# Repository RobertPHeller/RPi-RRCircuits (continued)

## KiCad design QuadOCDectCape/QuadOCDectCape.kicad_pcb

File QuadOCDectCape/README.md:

# QuadOCDectCape

Quad Occupancy detector Cape (for a Beagle Bone).

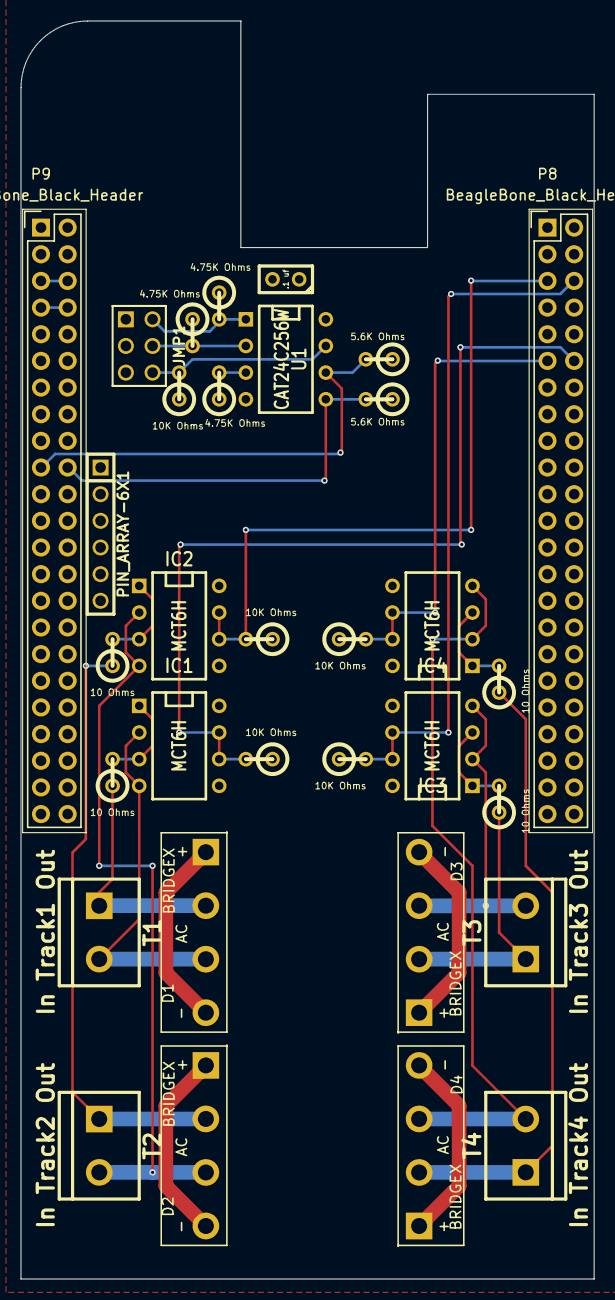
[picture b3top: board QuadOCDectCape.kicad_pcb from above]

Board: 2 copper layers, 54.6 x 119.9 mm, 32 parts (0 on the bottom side), 30 nets.

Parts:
C1: .1 uf; C1
D1, D2, D3, D4: BRIDGEX; KBL
IC1, IC2, IC3, IC4: MCT6H; DIP-8__300
JMP1: WP 1 0; pin_array_3x2
P8, P9: BeagleBone_Black_Header; Socket_BeagleBone_Black
PIN_ARRAY-6X1: Val**; PIN_ARRAY-6X1
R1, R3, R5, R7: 10 Ohms; R1
R2, R4, R6, R8, R14: 10K Ohms; R1
R9, R10: 5.6K Ohms; R1
R11, R12, R13: 4.75K Ohms; R1
T1: In Track1 Out; bornier2
T2: In Track2 Out; bornier2
T3: In Track3 Out; bornier2
T4: In Track4 Out; bornier2
U1: CAT24C256W; DIP-8__300

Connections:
+3.3V: C1.1, P9.3, P9.4, R2.1, R4.1, R6.1, R8.1, R9.1, R10.1, R11.1, R12.1, R13.1, R14.1, U1.8
+5V: P9.5, P9.6
/Cape EEProm/SCL: P9.19, R10.2, U1.6
/Cape EEProm/SDA: P9.20, R9.2, U1.5
/Occupancy Detector 1/OD1: IC1.6, IC1.7, P8.12, R2.2
/Occupancy Detector 2/OD2: IC2.6, IC2.7, P8.5, R4.2
/Occupancy Detector 3/OD3: IC3.6, IC3.7, P8.6, R6.2
/Occupancy Detector 4/OD4: IC4.6, IC4.7, P8.11, R8.2
GND: C1.2, IC1.5, IC1.8, IC2.5, IC2.8, IC3.5, IC3.8, IC4.5, IC4.8, JMP1.1, JMP1.3, JMP1.5, P8.1, P8.2, P9.1, P9.2, P9.43, P9.44, P9.45, P9.46, U1.4
unnamed: IC4.1, IC4.3, R7.2
unnamed: D4.3, IC4.2, IC4.4, T4.2
unnamed: D4.2, R7.1, T4.1
unnamed: D4.1, D4.4
unnamed: JMP1.6, R14.2, U1.7
unnamed: JMP1.2, R11.2, U1.1
unnamed: JMP1.4, R12.2, U1.2
unnamed: R13.2, U1.3
unnamed: IC1.1, IC1.3, R1.2
unnamed: D1.3, IC1.2, IC1.4, T1.2
unnamed: D1.2, R1.1, T1.1
unnamed: D1.1, D1.4
unnamed: D2.2, R3.1, T2.1
unnamed: D2.1, D2.4
unnamed: D2.3, IC2.2, IC2.4, T2.2
unnamed: IC2.1, IC2.3, R3.2
unnamed: D3.3, IC3.2, IC3.4, T3.2
unnamed: IC3.1, IC3.3, R5.2
unnamed: D3.2, R5.1, T3.1
unnamed: D3.1, D3.4
SYS_5V: P9.7, P9.8

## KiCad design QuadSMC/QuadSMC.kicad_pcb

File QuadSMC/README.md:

# QuadSMC

This is a generic quad verison of SMCSenseHAT.

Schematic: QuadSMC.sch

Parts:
C1, C2: .1 uf; Mouser Part Number 21RZ310-RC
C3, C4: 1 uf 35V; Mouser Part Number 74-199D105X9035A1VE3
D1, D6: 1N5229B; Mouser Part Number 512-1N5229B
D2, D3, D4, D5: 1N4002; Mouser Part Number 833-1N4002-TP
IC1, IC2: MCT6H; DIP8; Mouser Part Number 782-MCT6H
Q1, Q2: MPQ3725A; DIP-14__300; Mouser Part Number 610-MPQ3725A
R1: 10K Ohms; Mouser Part Number 652-4609X-1LF-10K
R2, R3, R4, R5: 270 Ohms; Mouser Part Number 71-CCF07270RGKE36
R6, R7, R8, R9: 100 Ohms; Mouser Part Number 71-CCF07100RJKE36
R10, R11, R12, R13, R14, R15, R16, R17, R18, R19, R20, R21, R22, R23: 1K Ohms; Mouser Part Number 71-CCF071K00JKE36
R24, R25, R26, R27, R28, R29, R30, R31: 470 Ohms; Mouser Part Number 279-CFR50J470R
T0: GPIO; Mouser Part Number 651-1725737
T1: Motor 1; Mouser Part Number 571-282834-5
T2: Motor 2; Mouser Part Number 571-282834-5
T3: Motor 3; Mouser Part Number 571-282834-5
T4: Motor 4; Mouser Part Number 571-282834-5
T5: Motor Power; SIL-2; Mouser Part Number 571-282834-2
U1, U2: 74AHCT00; Mouser Part Number 595-SN74AHC00N
U3, U4: LM324N; Mouser Part Number 512-LM324N

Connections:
+3.3V: C1.1, C2.1, R1.1, T0.1, U1.14 (VCC), U2.14 (VCC)
+12V: C3.1, C4.1, R10.1, R11.1, R12.1, R13.1, R14.1, R15.1, R24.1, R25.1, R26.1, R27.1, R28.1, R29.1, R30.1, R31.1, T5.1, U3.4 (V+), U4.4 (V+)
/GPIO0: R5.2, T0.9
/GPIO1: T0.8, U2.8, U2.12
/GPIO2: R3.2, T0.7
/GPIO3: T0.6, U2.3, U2.4
/GPIO4: R2.2, T0.5
/GPIO5: T0.4, U1.8, U1.12
/GPIO6: R4.2, T0.3
/GPIO7: T0.2, U1.3, U1.4
/P1-1: R1.2, T1.5, U1.1
/P1-2: R1.3, T1.3, U1.5
/P2-1: R1.4, T2.5, U1.9
/P2-2: R1.5, T2.3, U1.13
/P3-1: R1.6, T3.5, U2.1
/P3-2: R1.7, T3.3, U2.5
/P4-1: R1.8, T4.5, U2.9
/P4-2: R1.9, T4.3, U2.13
GND: C1.2, C2.2, C3.2, C4.2, D1.1 (A), D6.1 (A), IC1.2, IC1.3, IC1.5, IC1.8, IC2.2, IC2.3, IC2.5, IC2.8, Q1.3 (E), Q1.5 (E), Q1.10 (E), Q1.12 (E), Q2.3 (E), Q2.5 (E), Q2.10 (E), Q2.12 (E), T0.10, T1.4, T2.4, T3.4, T4.4, T5.2 (PM), U1.7 (GND), U2.7 (GND), U3.11 (V-), U4.11 (V-)
M1A: Q1.1 (C), R24.2, T1.2
M1B: Q1.7 (C), R25.2, T1.1
M2A: Q1.8 (C), R26.2, T2.2
M2B: Q1.14 (C), R27.2, T2.1
M3A: Q2.1 (C), R28.2, T3.2
M3B: Q2.7 (C), R29.2, T3.1
M4A: Q2.8 (C), R30.2, T4.2
M4B: Q2.14 (C), R31.2, T4.1
unnamed: Q2.6 (B), R22.1
unnamed: Q2.9 (B), R23.1
unnamed: Q2.13 (B), R16.1
unnamed: R16.2, U4.7
unnamed: D4.1 (A), R6.1, R10.2, U3.2 (-), U3.12 (+)
unnamed: R18.2, U3.14
unnamed: Q1.6 (B), R18.1
unnamed: D5.1 (A), R7.1, R11.2, U3.5 (+), U3.9 (-)
unnamed: IC1.6, R7.2
unnamed: IC1.7, R6.2
unnamed: IC2.7, R8.2
unnamed: D2.1 (A), R8.1, R12.2, U4.2 (-), U4.12 (+)
unnamed: IC2.6, R9.2
unnamed: D3.1 (A), R9.1, R13.2, U4.5 (+), U4.9 (-)
unnamed: D1.2 (K), D4.2 (K), D5.2 (K), R15.2, U3.3 (+), U3.6 (-), U3.10 (+), U3.13 (-)
unnamed: D2.2 (K), D3.2 (K), D6.2 (K), R14.2, U4.3 (+), U4.6 (-), U4.10 (+), U4.13 (-)
unnamed: R20.2, U3.7
unnamed: R21.2, U4.1
unnamed: R22.2, U4.14
unnamed: R23.2, U4.8
unnamed: Q1.2 (B), R17.1
unnamed: R17.2, U3.1
unnamed: R19.2, U3.8
unnamed: Q1.9 (B), R19.1
unnamed: Q1.13 (B), R20.1
unnamed: Q2.2 (B), R21.1
unnamed: IC2.4, R5.1
unnamed: IC1.1, R4.1
unnamed: IC1.4, R2.1
unnamed: IC2.1, R3.1
unnamed: U2.2, U2.6
unnamed: U2.10, U2.11
unnamed: U1.2, U1.6
unnamed: U1.10, U1.11

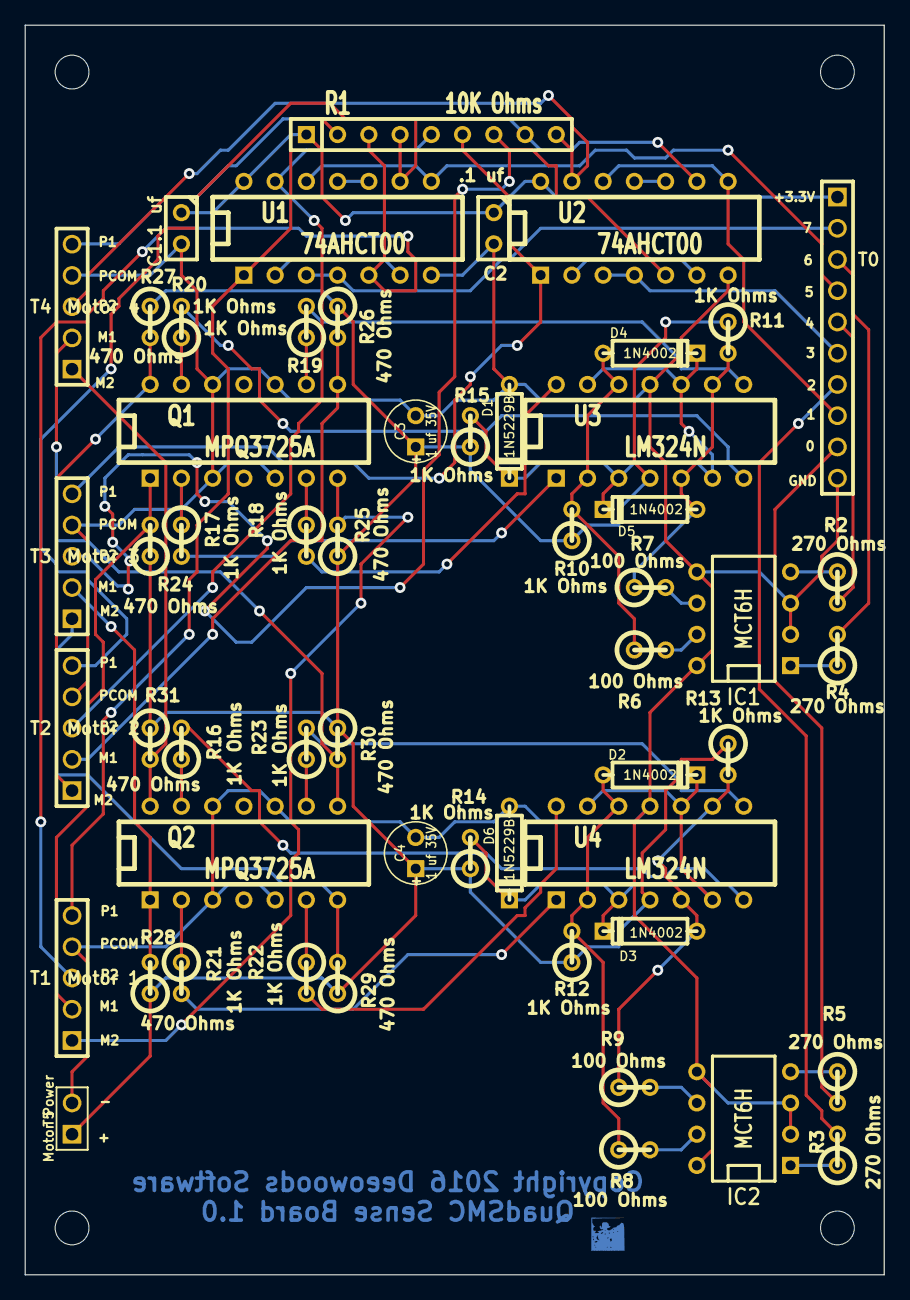
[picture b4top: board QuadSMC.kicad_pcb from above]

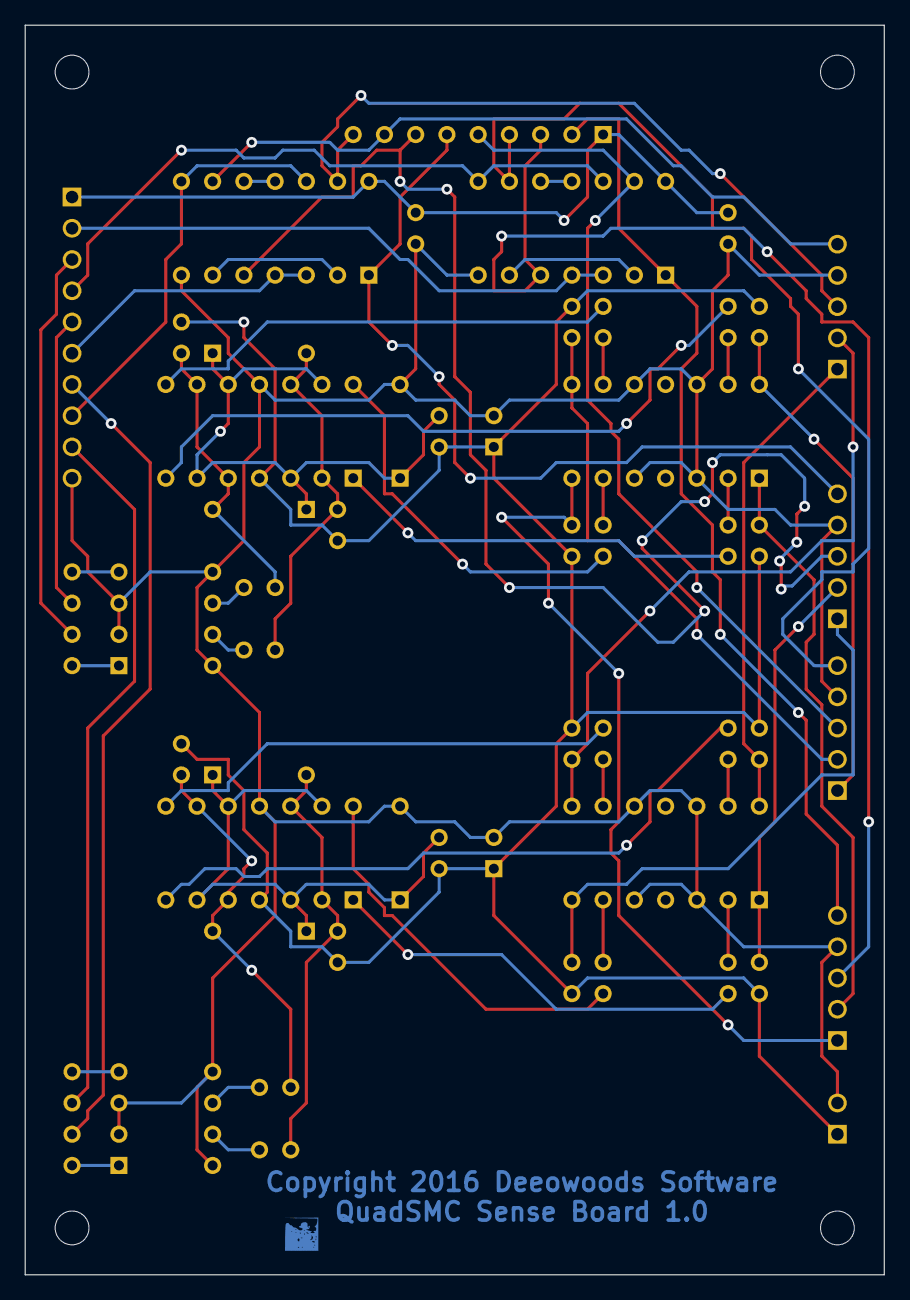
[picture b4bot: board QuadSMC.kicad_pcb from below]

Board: 2 copper layers, 69.8 x 101.6 mm, 59 parts (4 on the bottom side), 61 nets.

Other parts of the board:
H2, H2#2, H2#3, H2#4: RPi_Hat_Mounting_Hole

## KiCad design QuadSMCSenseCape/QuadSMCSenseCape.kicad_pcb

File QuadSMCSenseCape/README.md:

# QuadSMCSenseCape

Quad Stall Motor w/ Sense Cape for a Beagle Bone.

* [Order this board from The Country Robot](https://www.thecountryrobot.com/product/quad-stall-motor-control-and-sense-cape-for-beagle-bare-circuit-board-w-doc/)
* [Order this board from PCBWay](https://www.pcbway.com/project/shareproject/Quad_Stall_motor_with_point_sense_cape.html)

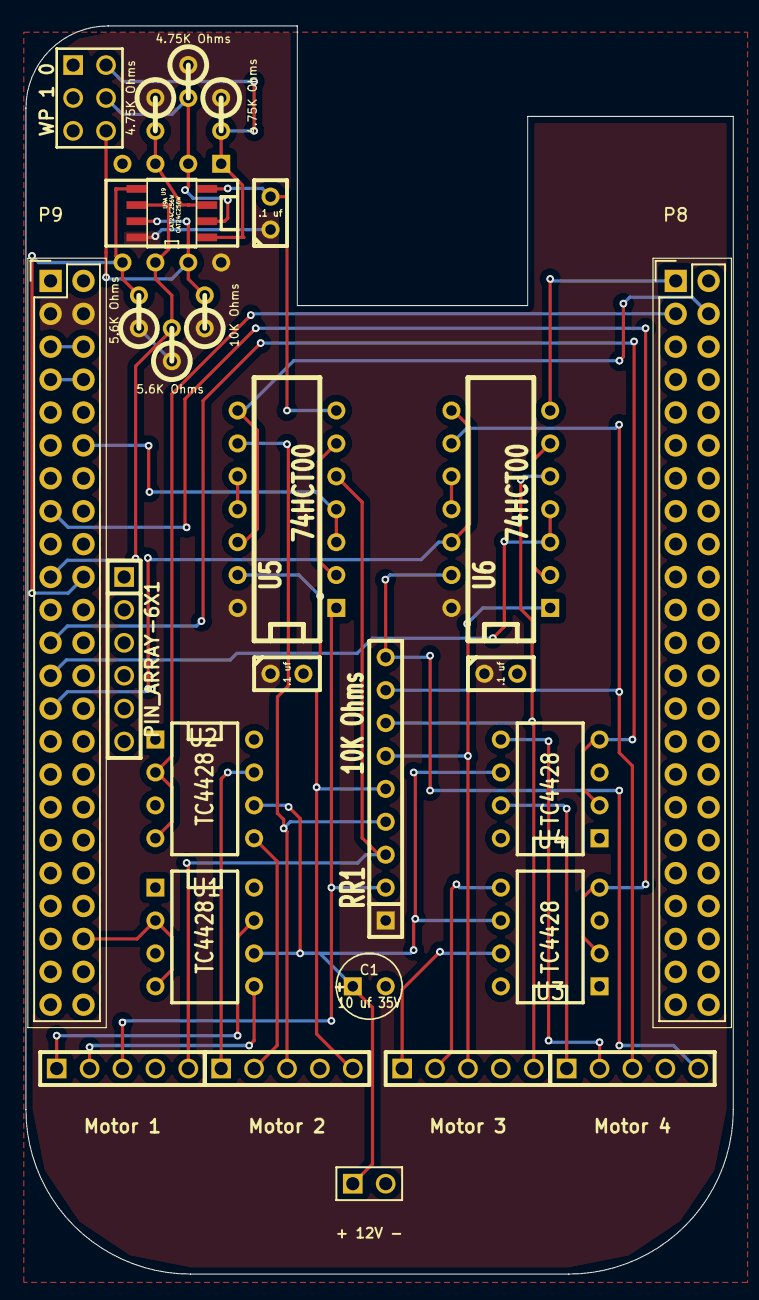
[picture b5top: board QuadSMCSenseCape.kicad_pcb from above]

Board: 2 copper layers, 54.6 x 96.4 mm, 28 parts (0 on the bottom side), 39 nets.

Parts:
C1: 10 uf 35V; C1V5
C2, C3, C8: .1 uf; C1
P2: WP 1 0; pin_array_3x2
P8, P9: BeagleBone_Black_Header; Socket_BeagleBone_Black
PIN_ARRAY-6X1: Val**; PIN_ARRAY-6X1
R3, R4: 5.6K Ohms; R1
R5, R6, R7: 4.75K Ohms; R1
R8: 10K Ohms; R1
RR1: 10K Ohms; SIL-9
T1: Motor 1; ScrewTerm_2.54-5
T2: Motor 2; ScrewTerm_2.54-5
T3: Motor 3; ScrewTerm_2.54-5
T4: Motor 4; ScrewTerm_2.54-5
T5: + 12V -; ScrewTerm2.54-2
U1, U2, U3, U4: TC4428; DIP-8__300
U5, U6: 74HCT00; DIP-14__300
U9: CAT24C256W; DIP-8__300
U9A: CAT24C256W; SOIC-8_N

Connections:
+3.3V: C2.1, C3.1, C8.1, P9.3, P9.4, R3.1, R4.1, R5.1, R6.1, R7.1, R8.1, RR1.1, U5.14, U6.14, U9.8, U9A.8
+5V: P9.5, P9.6
+12V: C1.1, T5.1, U1.6, U2.6, U3.6, U4.6
/Cape EEPROM/SCL: P9.19, R4.2, U9.6, U9A.6
/Cape EEPROM/SDA: P9.20, R3.2, U9.5, U9A.5
/MSel1: P9.42, U1.2, U1.4
/MSel2: P8.3, U2.2, U2.4
/MSel3: P9.15, U3.2, U3.4
/MSel4: P9.23, U4.2, U4.4
/Motor1A: T1.1, U1.7
/Motor1B: T1.2, U1.5
/Motor2A: T2.1, U2.7
/Motor2B: T2.2, U2.5
/Motor3A: T3.1, U3.7
/Motor3B: T3.2, U3.5
/Motor4A: T4.1, U4.7
/Motor4B: T4.2, U4.5
/PSense1: P9.12, U5.3, U5.4
/PSense2: P8.4, U5.8, U5.12
/PSense3: P9.25, U6.3, U6.4
/PSense4: P9.27, U6.8, U6.12
/Points1A: RR1.2, T1.3, U5.1
/Points1B: RR1.3, T1.5, U5.5
/Points2A: RR1.4, T2.3, U5.9
/Points2B: RR1.5, T2.5, U5.13
/Points3A: RR1.6, T3.3, U6.1
/Points3B: RR1.7, T3.5, U6.5
/Points4A: RR1.8, T4.3, U6.9
/Points4B: RR1.9, T4.5, U6.13
GND: C1.2, C2.2, C3.2, C8.2, P2.1, P2.3, P2.5, P8.1, P8.2, P9.1, P9.2, P9.43, P9.44, P9.45, P9.46, T1.4, T2.4, T3.4, T4.4, T5.2, U1.3, U2.3, U3.3, U4.3, U5.7, U6.7, U9.4, U9A.4
unnamed: U5.2, U5.6
unnamed: U6.10, U6.11
unnamed: U5.10, U5.11
unnamed: U6.2, U6.6
unnamed: P2.6, R8.2, U9.7, U9A.7
unnamed: P2.2, R5.2, U9.1, U9A.1
unnamed: P2.4, R6.2, U9.2, U9A.2
unnamed: R7.2, U9.3, U9A.3
SYS_5V: P9.7, P9.8
